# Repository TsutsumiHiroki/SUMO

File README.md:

# Robot SUMO Projects

## 開発環境
- Arduino
- [Arduino-Pico](https://github.com/earlephilhower/arduino-pico)

## 使用したハードウェア
- Odrive
- Raspberry Pi Pico

## 開発環境の構築
### Raspberry Pi Pico

詳細は[こちら](https://github.com/earlephilhower/arduino-pico?tab=readme-ov-file#installation)を見た方が正確です．

1. Arduino Board Manager を選択
   
   Ctrl + Shift + P でコマンドパレットを呼び出し，「Arduino: Board Manager」を検索し，選択

2. Additional URLs に Arduino Pico を追加
   1. 右下，Additional URLs を選択
   2. 「項目の追加」を選択

   3. 下記URLをコピーしてペースト
   
   https://github.com/earlephilhower/arduino-pico/releases/download/global/package_rp2040_index.json

3. Raspberry Pi Pico/RP2040 を追加
   1. 再度，Arduino Board Manager を選択
   2. 画像と同じ Raspberry Pi Pico/RP2040 をインストール

4. Arduino Board Configuration の設定
   1. Ctrl + Shift + P でコマンドパレットを呼び出し，「Arduino: Board Config」を検索し，選択
   2. 「Selected Board」に「Pico」と検索し「Raspberry Pi Pico」を選択．少し待つとその他設定が現れるが特に初期設定からいじる必要はない．

### Githubからのクローン
1. Code を選択し，HTTP を選択
   
2. URL をコピー
   
3. ソース管理からクローンを選択
   
4. コピーした URL をペースト

   Enter で確定
5. 保存するディレクトリを設定
   
   後から見つけられるようにしておこう

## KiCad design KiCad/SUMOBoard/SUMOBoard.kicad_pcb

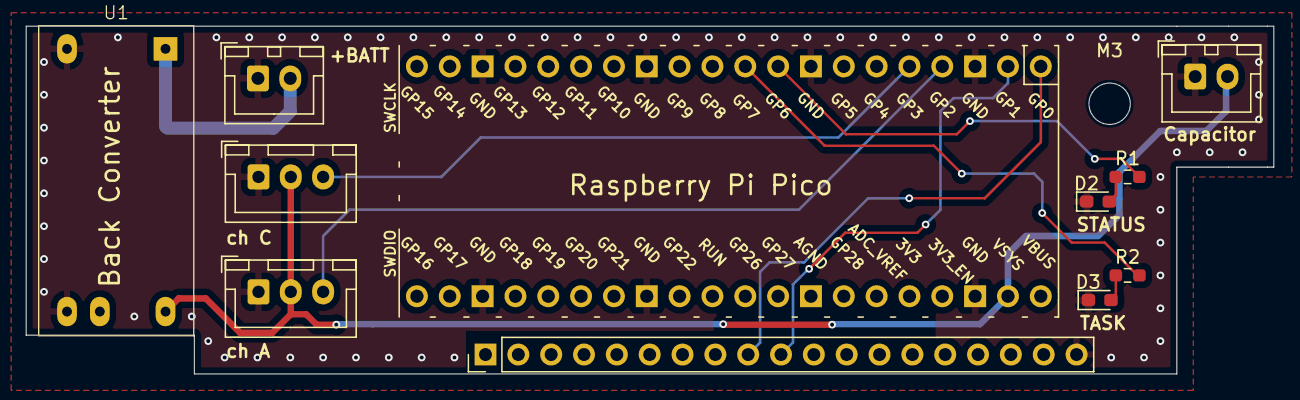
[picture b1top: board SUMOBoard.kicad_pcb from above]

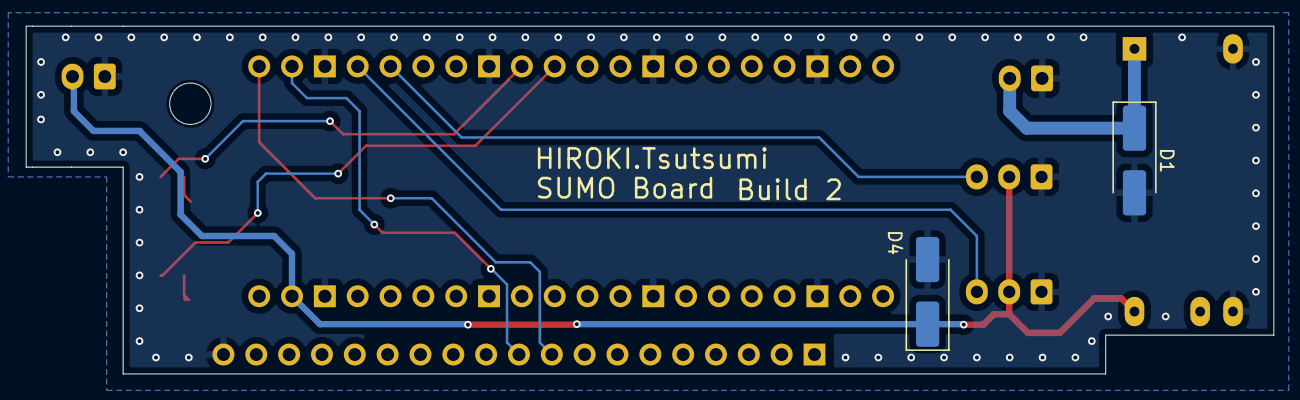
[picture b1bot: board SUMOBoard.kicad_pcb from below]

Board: 2 copper layers, 96.5 x 26.9 mm, 14 parts (2 on the bottom side), 11 nets.

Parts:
D1, D4: D; D_SMA_Handsoldering
D2, D3: LED; LED_0603_1608Metric_Pad1.05x0.95mm_HandSolder
H1: MountingHole; MountingHole_3.2mm_M3
J1, J4: Conn_01x03; JST_XH_B3B-XH-A_1x03_P2.50mm_Vertical
J3, J6: Conn_01x02; JST_XH_B2B-XH-A_1x02_P2.50mm_Vertical
J7: Conn_01x19_Pin; PinHeader_1x19_P2.54mm_Vertical
R1, R2: R; R_0603_1608Metric_Pad0.98x0.95mm_HandSolder
U1: 0AS1R5-4805
U2: Pico; RPi_Pico_SMD_TH

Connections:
+5V: D4.1 (K), J1.2, J4.2, J6.2, U1.3 (VOUT), U2.39 (VSYS)
+BATT: D1.1 (K), J3.2, U1.1 (VIN)
GND: D1.2 (A), D2.1 (K), D3.1 (K), D4.2 (A), J1.1, J3.1, J4.1, J6.1, J7.19, U1.2 (GND), U1.5 (GND), U2.3 (GND), U2.8 (GND), U2.13 (GND), U2.18 (GND), U2.23 (GND), U2.28 (GND), U2.38 (GND)
LED1: R1.2, U2.9 (GPIO6)
LED2: R2.2, U2.10 (GPIO7)
unnamed: D2.2 (A), R1.1
unnamed: D3.2 (A), R2.1
Odrive-RX: J7.9, U2.1 (GPIO0)
Odrive-TX: J7.10, U2.2 (GPIO1)
mr8-A: J4.3, U2.4 (GPIO2)
mr8-C: J1.3, U2.5 (GPIO3)

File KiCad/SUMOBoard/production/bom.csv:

Designator,Footprint,Quantity,Value,LCSC Part #
"D1, D4",D_SMA_Handsoldering,2,D,
"D2, D3",0603,2,LED,
"J1, J4",JST_XH_B3B-XH-A_1x03_P2.50mm_Vertical,2,Conn_01x03,
"J3, J6",JST_XH_B2B-XH-A_1x02_P2.50mm_Vertical,2,Conn_01x02,
J7,PinHeader_1x19_P2.54mm_Vertical,1,Conn_01x19_Pin,
"R1, R2",0603,2,R,
U1,0AS1R5-4805,1,~,
U2,RPi_Pico_SMD_TH,1,Pico,

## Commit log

2024-08-09 不要なファイルを無視
2024-08-09 制御基板を作成
2024-08-09 土俵上で動作させることができた
2024-08-09 機能追加できるように予約
2024-08-10 開発コードを追加
2024-08-13 Yorikiriを追加
2024-08-13 READMEを追加
2024-08-13 ボタン動作をお試し中
2024-08-13 クローンまでの手順を作成
2024-08-17 TaskManagerを除いてロボットの動作を確認
2024-08-17 電圧，電流読み取り機能の追加
2024-08-18 土俵での動作を確認
2024-09-03 Build2作成
2024-09-03 Build1作成
